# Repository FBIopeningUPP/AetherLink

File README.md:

# AetherLink

AetherLink is a open-source, Upto 12-cell BMS telemetry node built around the ESP32-C3 and the Texas Instruments BQ76940 Analog Front-End (AFE). It read invidual cell voltage, it also calculates ur pack health and it transmits all the data through WebBle dashboard in your browser

# Features

* Supports upto 12s lithium battery packs
* Individual cell voltage monitoring
* Pack Voltage monitoring
* Cell balancing support
* I2C communication between MCU and BQ76940
* Compact PCB Layout
* Open - source hardware and firmware

# Hardware Specifications

* **MCU** - RP2040
* **BMS Monitoring IC** -  BQ76940

# The Architecture

The projects works on battery monitoring, where it tracks the whole battery while being plugged on the jst connector it tracks the votlage graphs and everything and it saves the data on NVS and then whenever u connect ur device to the website it processes the data and displays ur batteries information

# Bill of Materials (BoM)

A complete, itemized BOM is generated by Kicad it can be viewed: [Production]((./production/bom.csv))

## Steps To Reproduce

### Hardware

1. The parts can be sourced by providing the BoM CSV file to lcsc from where u can order the parts.
2. The [PCB](./hardware/production/pcb.zip) can be ordered through JLCPCB with a stencil for precise soldering.
3. Soldering can be done using low temp solder paste while using the stencil to create a perfect solder layer

### Software

1. Install platformio
2. Open Terminal and go open the main directory
    ```
    pio run build
3. Firmware file will be generated and using flash tool everything will be flashed [Flash Tool](https://esptool.spacehuhn.com/)

### Dashboard

1. The dashboard can be accessed through [AetherLink](https://fbiopeningupp.github.io/AetherLink/)
2. U connect ur bluetooth device to your laptop and then click connect to drone
3. U can analyze ur battery and everything

# RENDERS

Front

Back

# USAGE OF AI

the usage of ai was done with antigravity debugging my code and help me with my pinout and everything

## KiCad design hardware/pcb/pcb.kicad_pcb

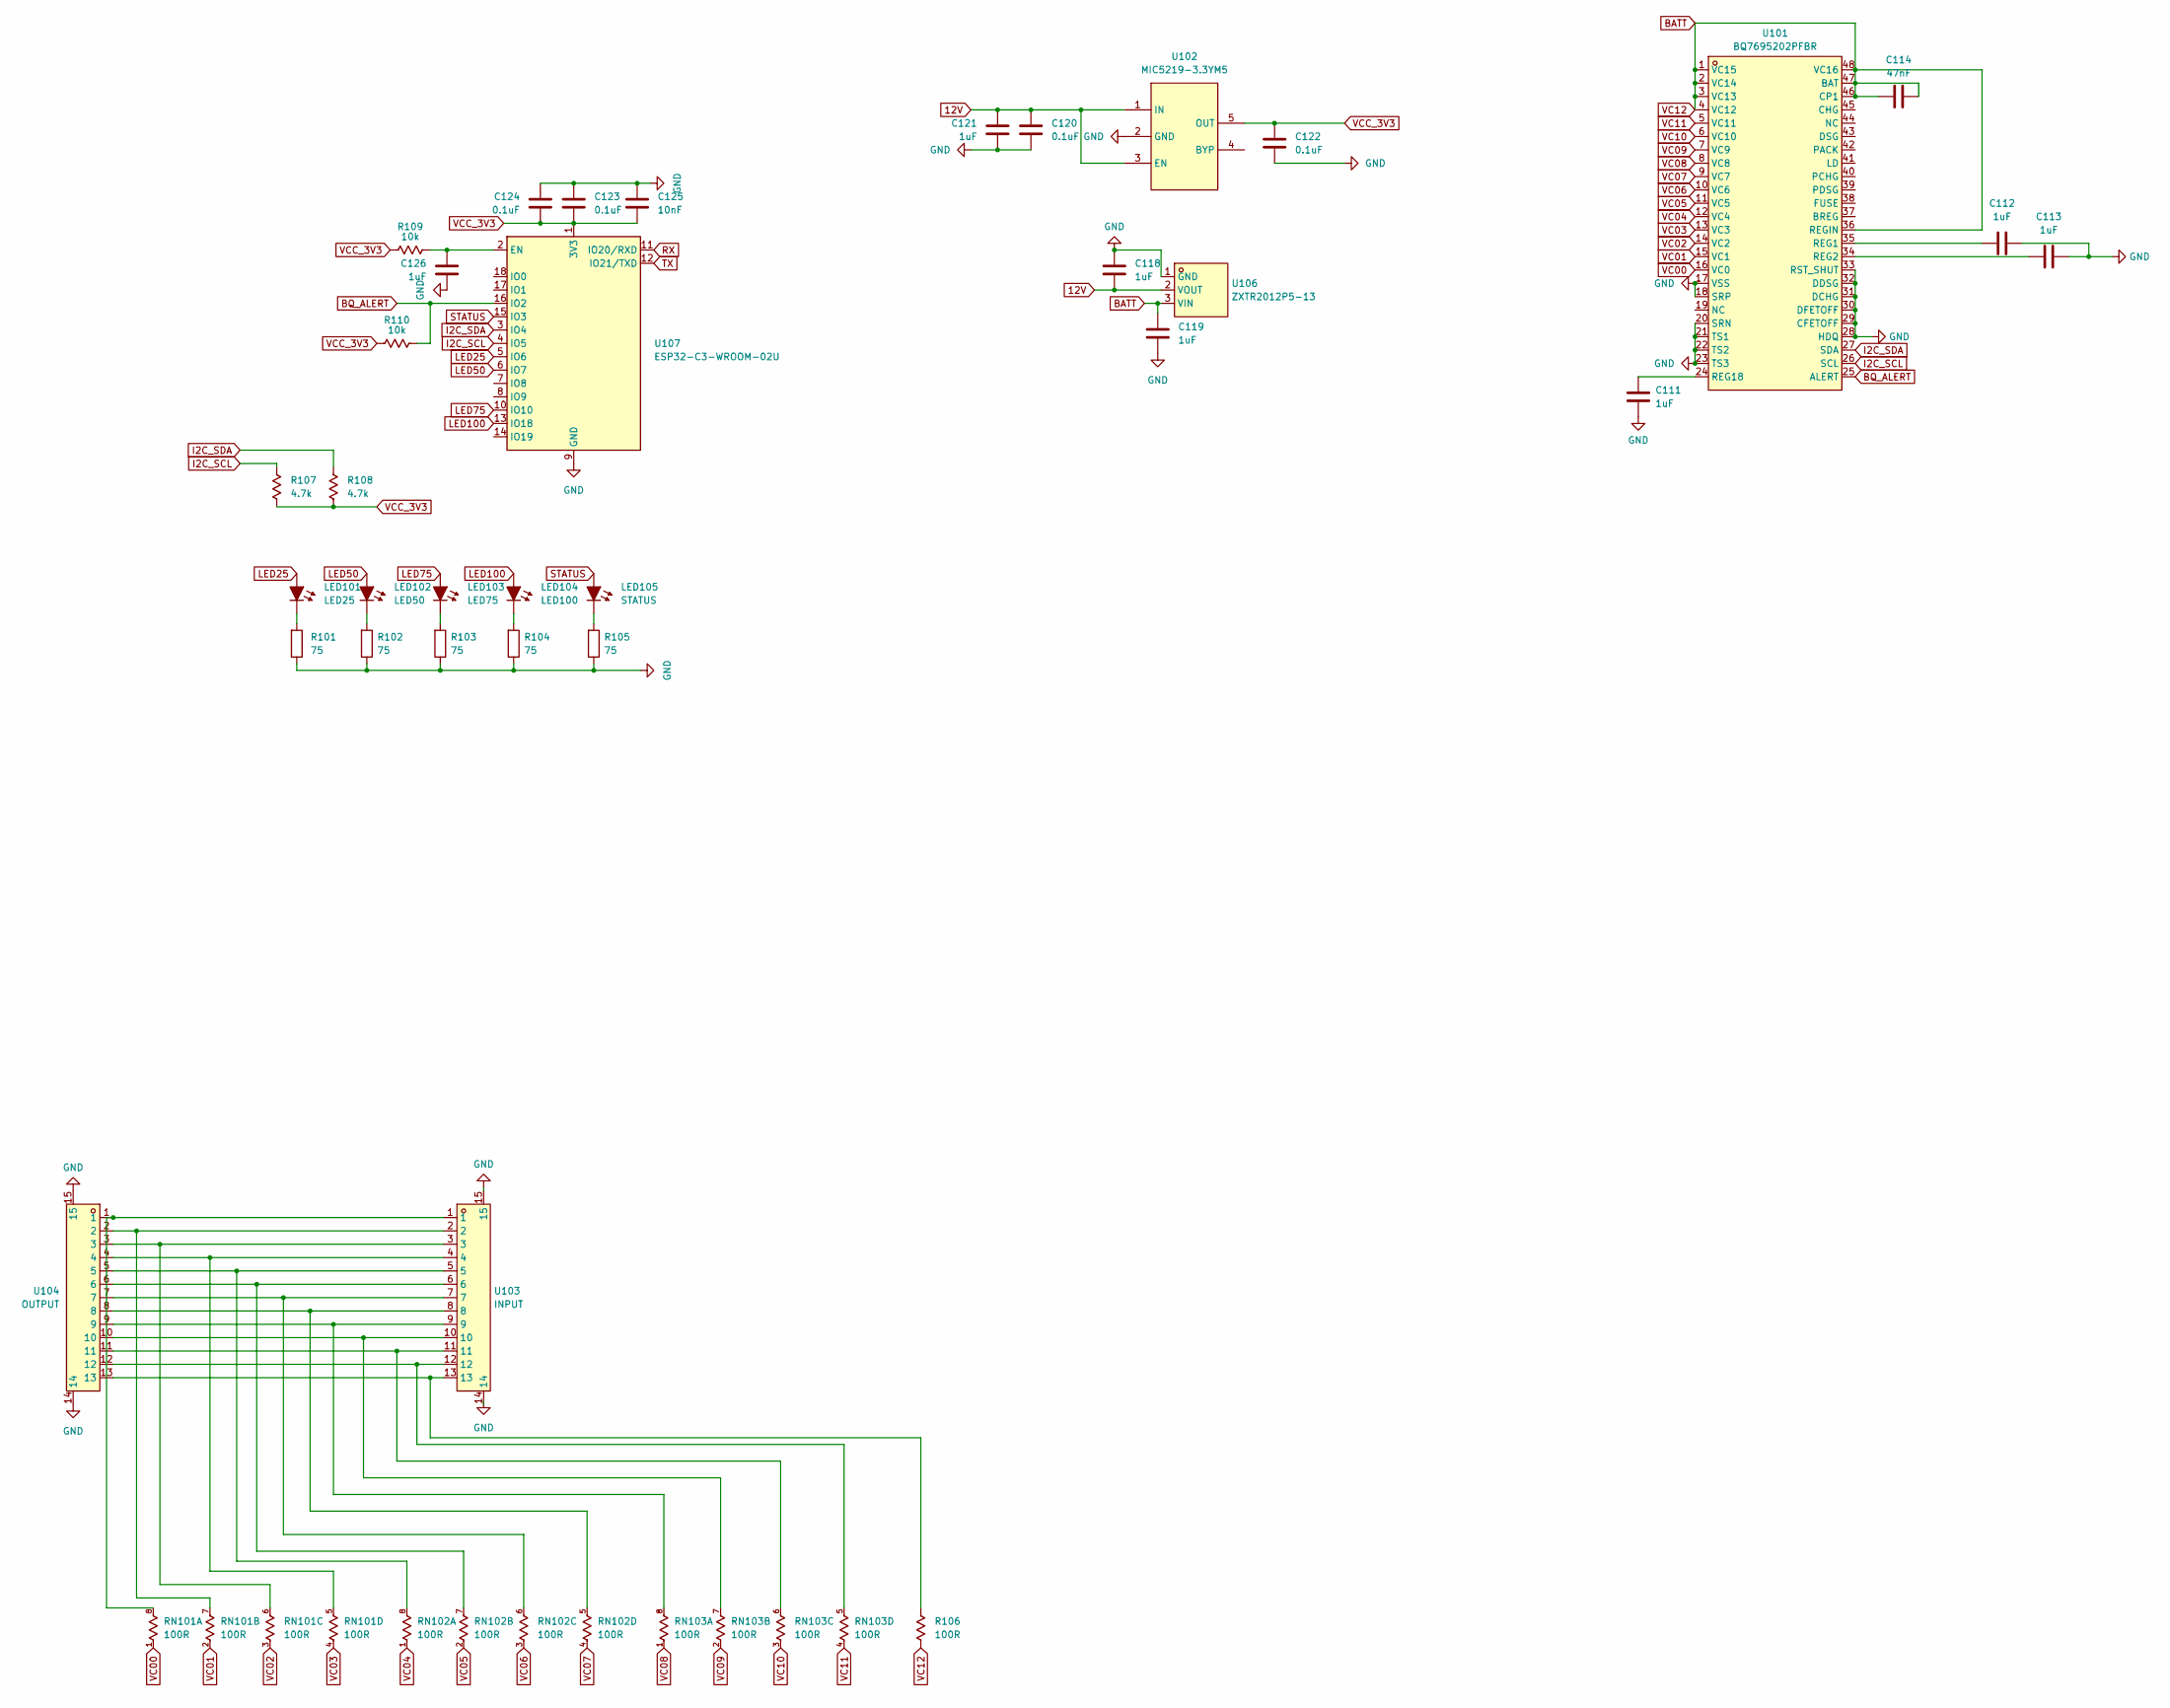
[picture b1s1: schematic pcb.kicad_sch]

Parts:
C111, C112, C113, C121, C126: 1uF; C_0402_1005Metric
C114: 47nF; C_0402_1005Metric
C118, C119: 1uF; C_0805_2012Metric
C120, C122, C123, C124: 0.1uF; C_0402_1005Metric
C125: 10nF; C_0402_1005Metric
LED101: LED25; LED_0603_1608Metric
LED102: LED50; LED_0603_1608Metric
LED103: LED75; LED_0603_1608Metric
LED104: LED100; LED_0603_1608Metric
LED105: STATUS; LED_0603_1608Metric
R101, R102, R103, R104, R105: 75; R_0402_1005Metric
R106: 100R; R_0402_1005Metric
R107, R108: 4.7k; R_0402_1005Metric
R109, R110: 10k; R_0402_1005Metric
RN101, RN102, RN103: 100R; R_Array_Convex_4x0402
U101: BQ7695202PFBR; TQFP-48_L7.0-W7.0-P0.50-LS9.0-TL; MPN BQ7695202PFBR; LCSC Part C3038665
U102: MIC5219-3.3YM5; SOT-23-5_L3.0-W1.7-P0.95-LS2.8-TL; LCSC Part C29613
U103: INPUT; CONN-SMD_13P-P2.50_HCZZ0520-13; MPN HCZZ0520-13; LCSC Part C7433778
U104: OUTPUT; CONN-SMD_13P-P2.50_HCZZ0520-13; MPN HCZZ0520-13; LCSC Part C7433778
U106: ZXTR2012P5-13; POWERDI-5_L5.4-W4.0-LS6.5-RD; MPN ZXTR2012P5-13; LCSC Part C155307
U107: ESP32-C3-WROOM-02U

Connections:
12V: C118.2, C120.1, C121.1, U102.1 (IN), U102.3 (EN), U106.2 (VOUT)
BATT: C114.1, C114.2, C119.1, R106.2, U101.1 (VC15), U101.2 (VC14), U101.3 (VC13), U101.4 (VC12), U101.36 (REGIN), U101.46 (CP1), U101.47 (BAT), U101.48 (VC16), U106.3 (VIN)
BQ_ALERT: R110.2, U101.25 (ALERT), U107.16 (IO2)
GND: C111.1, C112.1, C113.1, C118.1, C119.2, C120.2, C121.2, C122.2, C123.1, C124.1, C125.1, C126.2, R101.2, R102.2, R103.2, R104.2, R105.2, U101.17 (VSS), U101.18 (SRP), U101.20 (SRN), U101.21 (TS1), U101.22 (TS2), U101.23 (TS3), U101.28 (HDQ), U101.29 (CFETOFF), U101.30 (DFETOFF), U101.31 (DCHG), U101.32 (DDSG), U101.33 (RST_SHUT), U102.2 (GND), U103.14, U103.15, U104.14, U104.15, U106.1 (GND), U107.9 (GND), U107.19 (GND)
I2C_SCL: R107.1, U101.26 (SCL), U107.4 (IO5)
I2C_SDA: R108.1, U101.27 (SDA), U107.3 (IO4)
LED25: LED101.2 (A), U107.5 (IO6)
LED50: LED102.2 (A), U107.6 (IO7)
LED75: LED103.2 (A), U107.10 (IO10)
LED100: LED104.2 (A), U107.13 (IO18)
unnamed: LED101.1 (K), R101.1
unnamed: LED102.1 (K), R102.1
unnamed: LED103.1 (K), R103.1
unnamed: LED104.1 (K), R104.1
unnamed: LED105.1 (K), R105.1
unnamed: R106.1, U103.13, U104.13
unnamed: RN101.8 (R1.2), U103.1, U104.1
unnamed: RN101.7 (R2.2), U103.2, U104.2
unnamed: RN101.6 (R3.2), U103.3, U104.3
unnamed: RN101.5 (R4.2), U103.4, U104.4
unnamed: RN102.8 (R1.2), U103.5, U104.5
unnamed: RN102.7 (R2.2), U103.6, U104.6
unnamed: RN102.6 (R3.2), U103.7, U104.7
unnamed: RN102.5 (R4.2), U103.8, U104.8
unnamed: RN103.8 (R1.2), U103.9, U104.9
unnamed: RN103.7 (R2.2), U103.10, U104.10
unnamed: RN103.6 (R3.2), U103.11, U104.11
unnamed: RN103.5 (R4.2), U103.12, U104.12
unnamed: C112.2, U101.35 (REG1)
unnamed: C113.2, U101.34 (REG2)
unnamed: C111.2, U101.24 (REG18)
unnamed: C126.1, R109.2, U107.2 (EN)
RX: U107.11 (IO20/RXD)
STATUS: LED105.2 (A), U107.15 (IO3)
TX: U107.12 (IO21/TXD)
VC00: RN101.1 (R1.1), U101.16 (VC0)
VC01: RN101.2 (R2.1), U101.15 (VC1)
VC02: RN101.3 (R3.1), U101.14 (VC2)
VC03: RN101.4 (R4.1), U101.13 (VC3)
VC04: RN102.1 (R1.1), U101.12 (VC4)
VC05: RN102.2 (R2.1), U101.11 (VC5)
VC06: RN102.3 (R3.1), U101.10 (VC6)
VC07: RN102.4 (R4.1), U101.9 (VC7)
VC08: RN103.1 (R1.1), U101.8 (VC8)
VC09: RN103.2 (R2.1), U101.7 (VC9)
VC10: RN103.3 (R3.1), U101.6 (VC10)
VC11: RN103.4 (R4.1), U101.5 (VC11)
VCC_3V3: C122.1, C123.2, C124.2, C125.2, R107.2, R108.2, R109.1, R110.1, U102.5 (OUT), U107.1 (3V3)

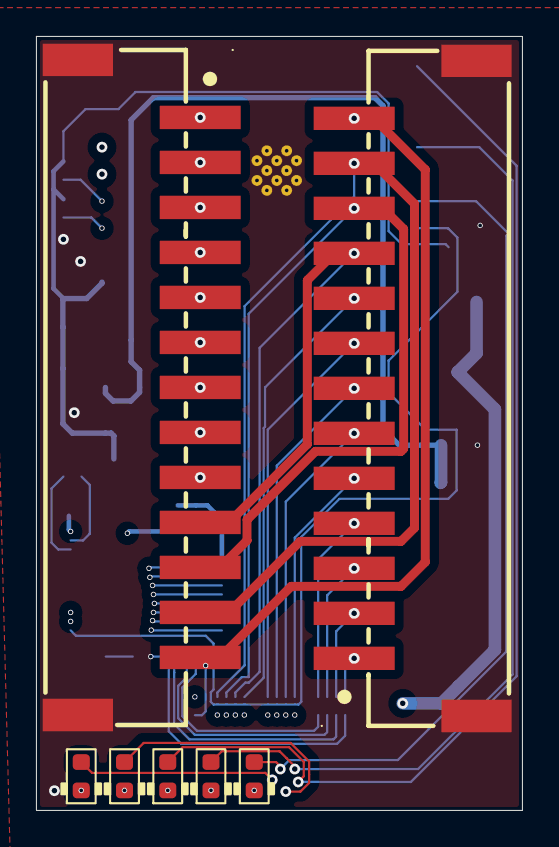
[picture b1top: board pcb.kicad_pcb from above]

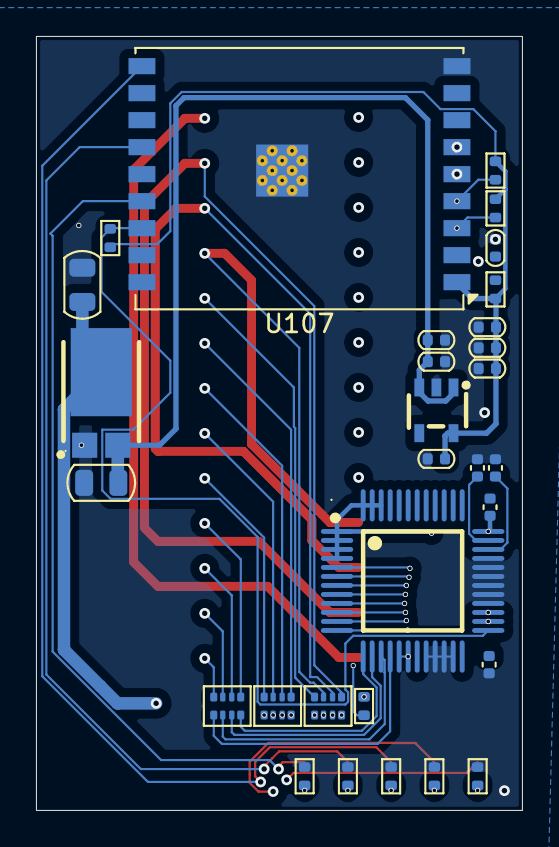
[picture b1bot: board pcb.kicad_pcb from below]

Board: 4 copper layers, 27.0 x 43.0 mm, 37 parts (30 on the bottom side), 46 nets.

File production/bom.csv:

Designator,Footprint,Quantity,Value,LCSC Part #
"C111, C112, C113, C121, C126",0402,5,1uF,
C114,0402,1,47nF,
"C118, C119",0805,2,1uF,
"C120, C122, C123, C124",0402,4,0.1uF,
C125,0402,1,10nF,
LED101,0603,1,LED25,
LED102,0603,1,LED50,
LED103,0603,1,LED75,
LED104,0603,1,LED100,
LED105,0603,1,STATUS,
"R101, R102, R103, R104, R105",0402,5,75,
R106,0402,1,100R,
"R107, R108",0402,2,4.7k,
"R109, R110",0402,2,10k,
"RN101, RN102, RN103",R_Array_Convex_4x0402,3,100R,
U101,TQFP-48_L7.0-W7.0-P0.50-LS9.0-TL,1,BQ7695202PFBR,C3038665
U102,SOT-23-5_L3.0-W1.7-P0.95-LS2.8-TL,1,MIC5219-3.3YM5,C29613
U103,CONN-SMD_13P-P2.50_HCZZ0520-13,1,INPUT,C7433778
U104,CONN-SMD_13P-P2.50_HCZZ0520-13,1,OUTPUT,C7433778
U106,POWERDI-5_L5.4-W4.0-LS6.5-RD,1,ZXTR2012P5-13,C155307
U107,ESP32-C3-WROOM-02U,1,ESP32-C3-WROOM-02U,

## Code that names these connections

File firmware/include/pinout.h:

#pragma once

//ESP32
#define PIN_I2C_SDA     4
#define PIN_I2C_SCL     5

#define PIN_BQ_ALERT    2


#define PIN_SOC_LED1_25     9
#define PIN_SOC_LED1_50     10
#define PIN_SOC_LED1_75     18
#define PIN_SOC_LED1_100    19

#define PIN_STATUS_LED      3

#define LED_ACTIVE_HIGH     1
// active-low

#define BATTERY_MAX_CELLS 12
#define BATTERY_MIN_CELLS 3
#define BATTERY_DEFAULT_CELLS 4

// BQ7694003 Net Mapping
#define NET_BQ_VC0 "BATT_TAP_0_BNEG"
#define NET_BQ_VC1 "BATT_TAP_1"
#define NET_BQ_VC2 "BATT_TAP_2"
#define NET_BQ_VC3 "BATT_TAP_3"
#define NET_BQ_VC4 "BATT_TAP_4"
#define NET_BQ_VC5 "BATT_TAP_5"
#define NET_BQ_VC6 "BATT_TAP_6"
#define NET_BQ_VC7 "BATT_TAP_7"
#define NET_BQ_VC8 "BATT_TAP_8"
#define NET_BQ_VC9 "BATT_TAP_9"
#define NET_BQ_VC10 "BATT_TAP_10"
#define NET_BQ_VC11 "BATT_TAP_11"
#define NET_BQ_VC12 "BATT_TAP_12_BPOS"

#define NET_BQ_BAT "PACK_BAT_POS"
// sense/supply per datasheet
#define NET_BQ_VSS "PACK_BAT_NEG"
// refrence 

#define NET_BQ_REGOUT "BQ_REGOUT_3V3"

#define NET_BQ_SDA "I2C_SDA"
#define NET_BQ_SCL "I2C_SCL"
#define NET_BQ_ALERT "BQ_ALERT_N"
// active-low open-drain

#define NET_BQ_CHG "BQ_CHG_CTRL"
#define NET_BQ_DSG "BQ_DSG_CTRL"
